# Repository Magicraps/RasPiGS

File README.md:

# RPiGS
Raspberry Pi Hat Groundstation for Proves-Atlas
https://github.com/NU-Horizonsat

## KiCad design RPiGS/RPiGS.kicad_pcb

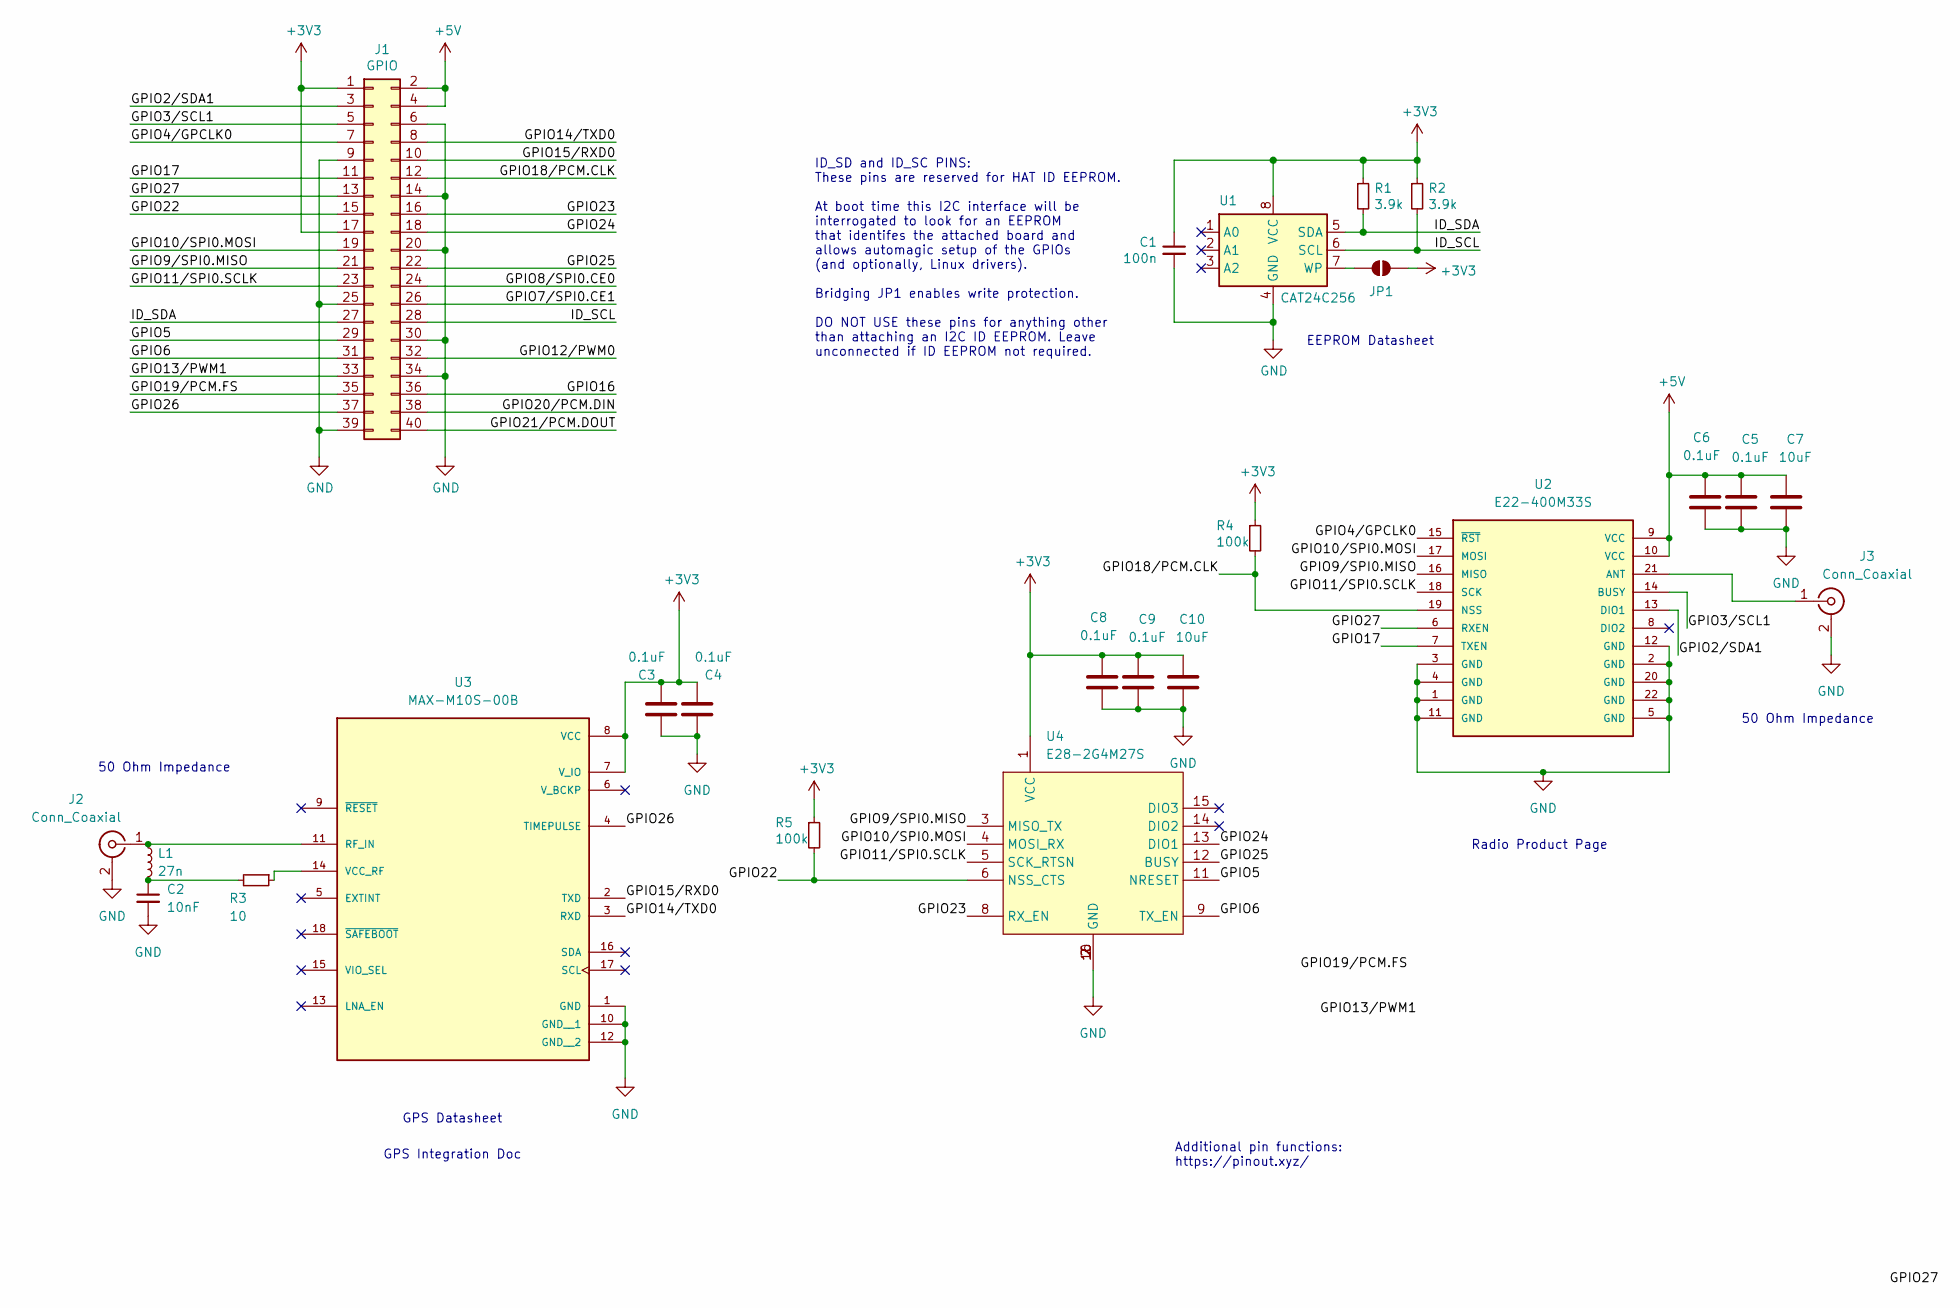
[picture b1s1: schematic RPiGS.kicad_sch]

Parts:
C1: 100n; C_0603_1608Metric
C2: 10nF; C_0603_1608Metric
C3, C4, C5, C6, C8, C9: 0.1uF; C_0603_1608Metric
C7, C10: 10uF; C_0603_1608Metric
J1: GPIO; PinSocket_2x20_P2.54mm_Vertical
J2, J3: Conn_Coaxial; SMA_Molex_73251-1153_EdgeMount_Horizontal
JP1: ID_WP; SolderJumper-2_P1.3mm_Open_RoundedPad1.0x1.5mm
L1: 27n; L_0603_1608Metric; LCSC C2041663
R1, R2: 3.9k; R_0603_1608Metric
R3: 10; R_0603_1608Metric; LCSC C25077
R4, R5: 100k; R_0603_1608Metric
U1: CAT24C256; TSSOP8_4P50X3P10_ONS
U2: E22-400M33S; XCVR_E22-400M33S
U3: MAX-M10S-00B; XCVR_MAX-M10S-00B
U4: E28-2G4M27S; WIRELM-SMD_E28-2G4M2XS; LCSC Part C411312

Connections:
+3V3: C1.1, C3.2, C4.2, C8.1, C9.1, C10.1, J1.1, J1.17, JP1.2 (B), R1.1, R2.1, R4.1, R5.1, U1.8 (VCC), U3.7 (V_IO), U3.8 (VCC), U4.1 (VCC)
+5V: C5.1, C6.1, C7.1, J1.2, J1.4, U2.9 (VCC), U2.10 (VCC)
/GPIO2/SDA1: J1.3, U2.13 (DIO1)
/GPIO3/SCL1: J1.5, U2.14 (BUSY)
/GPIO4/GPCLK0: J1.7, U2.15 (~RST)
/GPIO5: J1.29, U4.11 (NRESET)
/GPIO6: J1.31, U4.9 (TX_EN)
/GPIO7/SPI0.CE1: J1.26
/GPIO8/SPI0.CE0: J1.24
/GPIO9/SPI0.MISO: J1.21, U2.16 (MISO), U4.3 (MISO_TX)
/GPIO10/SPI0.MOSI: J1.19, U2.17 (MOSI), U4.4 (MOSI_RX)
/GPIO11/SPI0.SCLK: J1.23, U2.18 (SCK), U4.5 (SCK_RTSN)
/GPIO12/PWM0: J1.32
/GPIO13/PWM1: J1.33
/GPIO14/TXD0: J1.8, U3.3 (RXD)
/GPIO15/RXD0: J1.10, U3.2 (TXD)
/GPIO16: J1.36
/GPIO17: J1.11, U2.7 (TXEN)
/GPIO18/PCM.CLK: J1.12, R4.2, U2.19 (NSS)
/GPIO19/PCM.FS: J1.35
/GPIO20/PCM.DIN: J1.38
/GPIO21/PCM.DOUT: J1.40
/GPIO22: J1.15, R5.2, U4.6 (NSS_CTS)
/GPIO23: J1.16, U4.8 (RX_EN)
/GPIO24: J1.18, U4.13 (DIO1)
/GPIO25: J1.22, U4.12 (BUSY)
/GPIO26: J1.37, U3.4 (TIMEPULSE)
/GPIO27: J1.13, U2.6 (RXEN)
/ID_SCL: J1.28, R2.2, U1.6 (SCL)
/ID_SDA: J1.27, R1.2, U1.5 (SDA)
GND: C1.2, C2.2, C3.1, C4.1, C5.2, C6.2, C7.2, C8.2, C9.2, C10.2, J1.6, J1.9, J1.14, J1.20, J1.25, J1.30, J1.34, J1.39, J2.2 (Ext), J3.2 (Ext), U1.4 (GND), U2.1 (GND), U2.2 (GND), U2.3 (GND), U2.4 (GND), U2.5 (GND), U2.11 (GND), U2.12 (GND), U2.20 (GND), U2.22 (GND), U3.1 (GND), U3.10 (GND__1), U3.12 (GND__2), U4.2 (GND), U4.7 (GND), U4.10 (GND), U4.16 (GND)
unnamed: C2.1, L1.2, R3.2
unnamed: J2.1 (In), L1.1, U3.11 (RF_IN)
unnamed: J3.1 (In), U2.21 (ANT)
unnamed: JP1.1 (A), U1.7 (WP)
unnamed: R3.1, U3.14 (VCC_RF)

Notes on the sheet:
50 Ohm Impedance
Additional pin functions: https://pinout.xyz/
GPS Datasheet
Radio Product Page
EEPROM Datasheet
ID_SD and ID_SC PINS: These pins are reserved for HAT ID EEPROM. At boot time this I2C interface will be interrogated to look for an EEPROM that identifes the attached board and allows automagic setup of the GPIOs (and optionally, Linux drivers). Bridging JP1 enables write protection. DO NOT USE th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
GPS Integration Doc

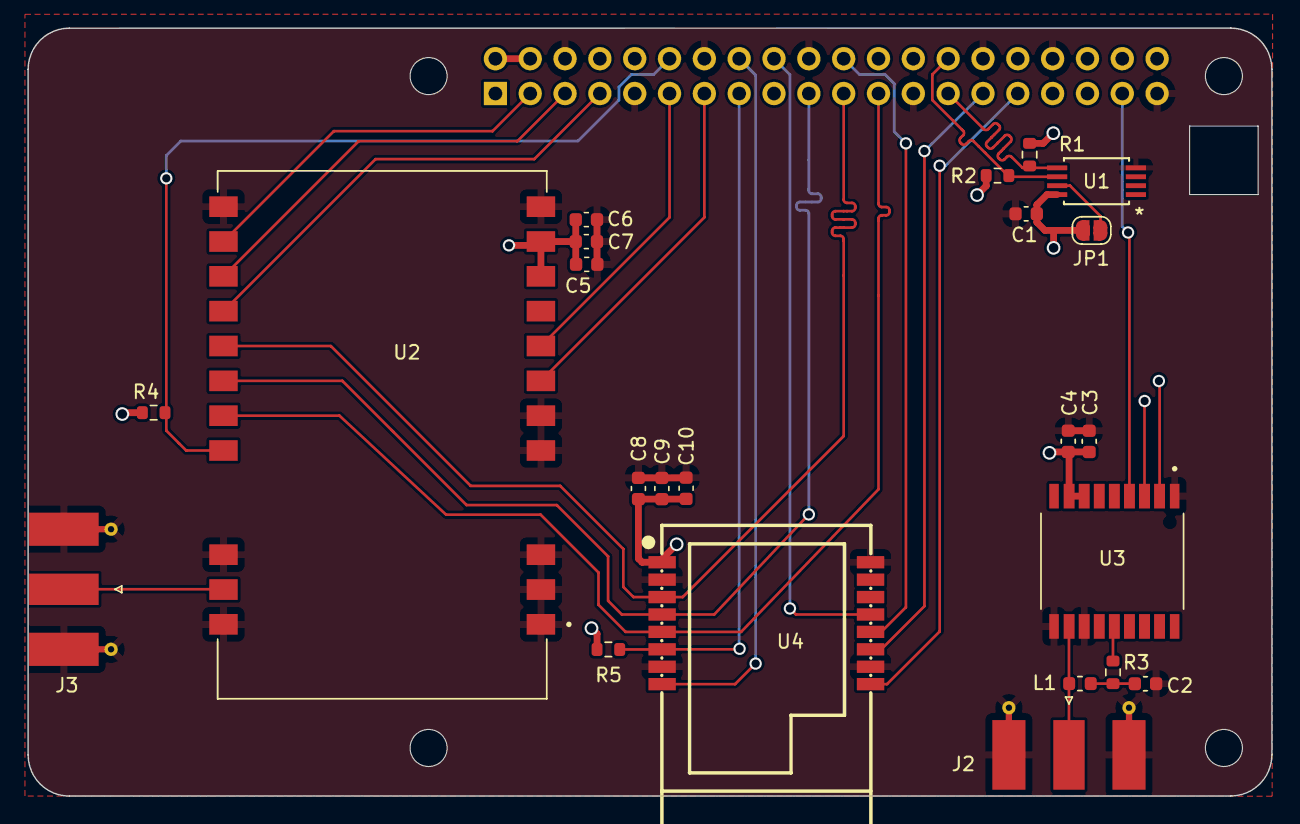
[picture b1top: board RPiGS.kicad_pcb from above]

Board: 4 copper layers, 90.7 x 56.0 mm, 28 parts (1 on the bottom side), 28 nets.

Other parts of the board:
MH1, MH2, MH3, MH4: MountingHole_2.7mm_M2.5

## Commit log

2025-12-25 Syncing. Impedance matching not done yet
